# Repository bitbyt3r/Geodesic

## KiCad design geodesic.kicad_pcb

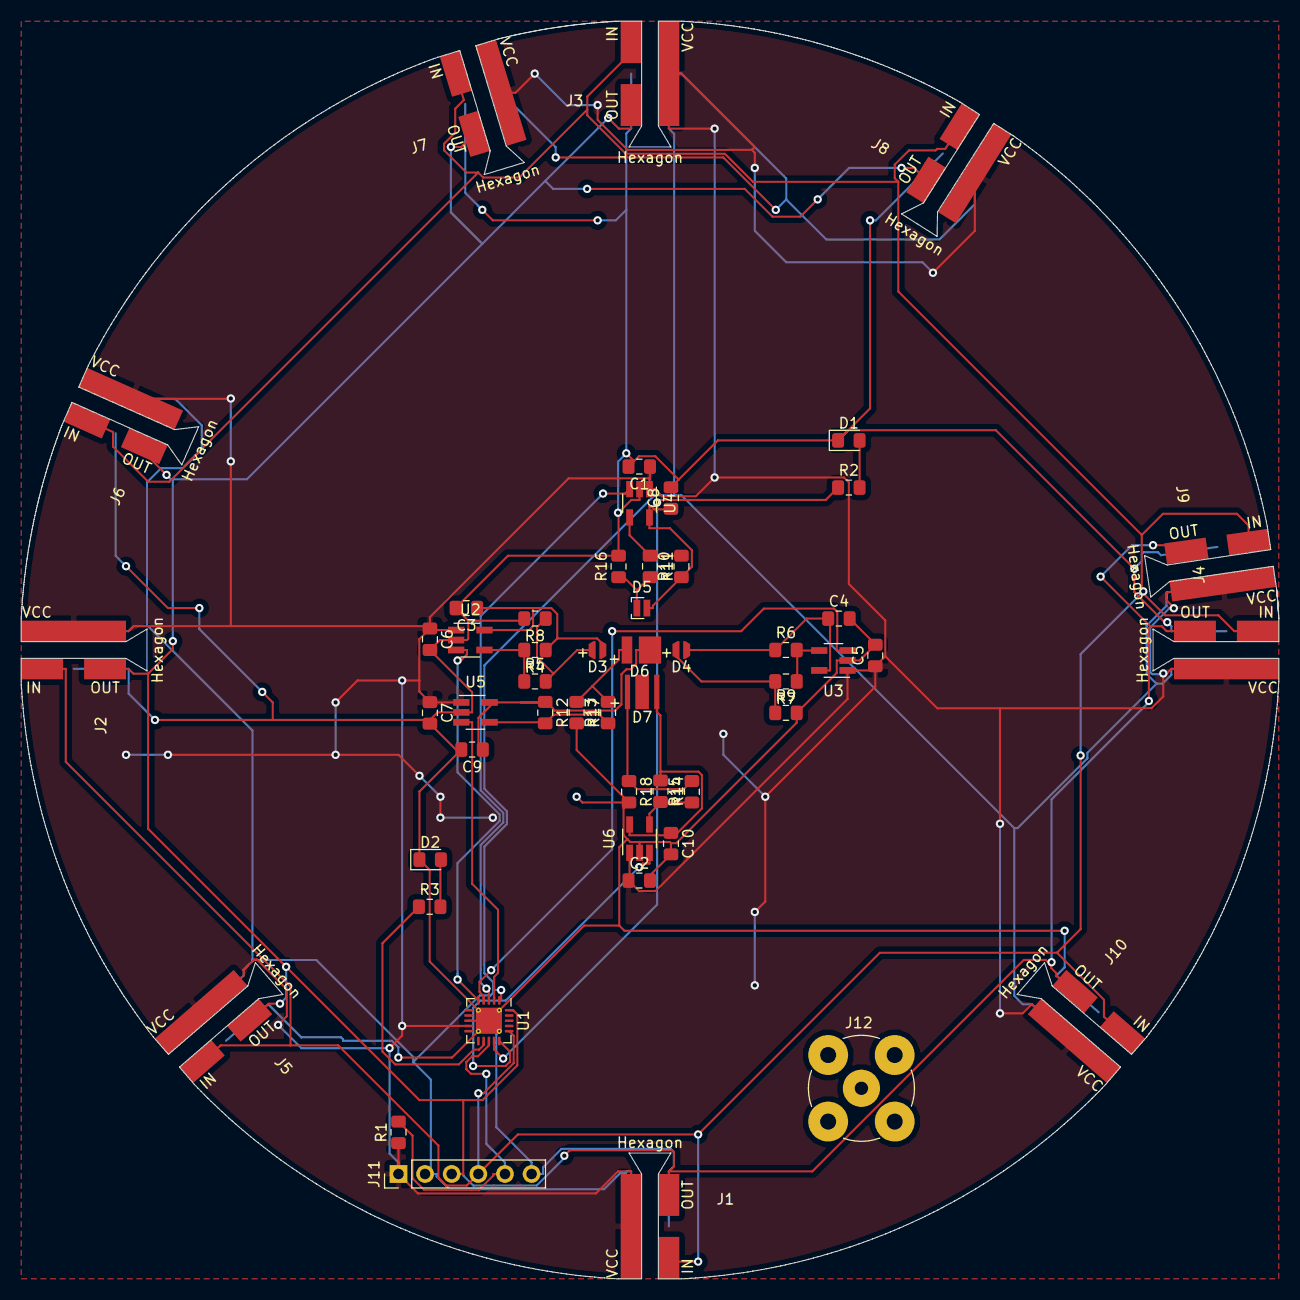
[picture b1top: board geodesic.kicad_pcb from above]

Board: 2 copper layers, 120.0 x 120.0 mm, 53 parts (0 on the bottom side), 30 nets.

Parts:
C1, C2, C5, C6, C7: 1uF; C_0805_2012Metric_Pad1.15x1.40mm_HandSolder
C3, C4, C8, C9, C10: 2.2uF; C_0805_2012Metric_Pad1.15x1.40mm_HandSolder
D1, D2: LED; LED_0805_2012Metric_Pad1.15x1.40mm_HandSolder
D3, D4: LED; XNOVA MP1616
D5: LED; LED_Cree-XQ
D6: LED; LUXEON_3535L
D7: LED; Cree_XPE
J1, J2, J3, J4, J5, J6, J7, J8, J9, J10: Hexagon; Geodesic_Hub_Connector
J11: Program; PinHeader_1x06_P2.54mm_Vertical
J12: AudioJack2_Ground; BNC_TEConnectivity_1478204_Vertical
R1: 1k; R_0805_2012Metric_Pad1.15x1.40mm_HandSolder
R2, R3, R4, R5, R6, R7, R8, R9, R10, R11, R12, R13, R14, R15, R16, R17, R18: R; R_0805_2012Metric_Pad1.15x1.40mm_HandSolder
U1: ATtiny24A-MU; QFN-20-1EP_4x4mm_P0.5mm_EP2.5x2.5mm_ThermalVias
U2, U3, U4, U5, U6: PAM2800; SOT-23-5_HandSoldering

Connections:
+5V: C1.1, C2.1, C5.1, C6.1, C7.1, J1.1, J2.1, J3.1, J4.1, J5.1, J6.1, J7.1, J8.1, J9.1, J10.1, J11.1, R1.1, U1.9, U2.1, U3.1, U4.1, U5.1, U6.1
/Clock: J1.2, J2.2, J3.2, J4.2, J5.2, J6.2, J7.2, J8.2, J9.2, J10.2, J11.2, U1.1
/Data_In: J1.3, J2.3, J3.3, J4.3, J5.3, J6.3, J7.3, J8.3, J9.3, J10.3, J11.4, U1.16
/Data_Out: J1.4, J2.4, J3.4, J4.4, J5.4, J6.4, J7.4, J8.4, J9.4, J10.4, J11.3, U1.20
/Reset: J11.5, R1.2, U1.13
GND: C1.2, C2.2, C3.2, C4.2, C5.2, C6.2, C7.2, C8.2, C9.2, C10.2, D1.1, D2.1, J1.5, J2.5, J3.5, J4.5, J5.5, J6.5, J7.5, J8.5, J9.5, J10.5, J11.6, R8.2, R9.2, R16.2, R17.2, R18.2, U1.8, U1.21, U2.2, U3.2, U4.2, U5.2, U6.2
unnamed: C3.1, D3.2, R4.1, U2.5
unnamed: C4.1, D4.2, R6.1, U3.5
unnamed: C8.1, D5.2, R10.1, U4.5
unnamed: C9.1, D6.2, R12.1, U5.5
unnamed: C10.1, D7.2, R14.1, U6.5
unnamed: D1.2, R2.2
unnamed: D2.2, R3.2
unnamed: D3.1, R5.2, R8.1
unnamed: D4.1, R7.2, R9.1
unnamed: D5.1, R11.2, R16.1
unnamed: D6.1, R13.2, R17.1
unnamed: D7.1, R15.2, R18.1
unnamed: R2.1, U1.14
unnamed: R3.1, U1.12
unnamed: R4.2, R5.1, U2.4
unnamed: R6.2, R7.1, U3.4
unnamed: R10.2, R11.1, U4.4
unnamed: R12.2, R13.1, U5.4
unnamed: R14.2, R15.1, U6.4
unnamed: U1.2, U5.3
unnamed: U1.3, U4.3
unnamed: U1.4, U3.3
unnamed: U1.5, U2.3
unnamed: U1.15, U6.3

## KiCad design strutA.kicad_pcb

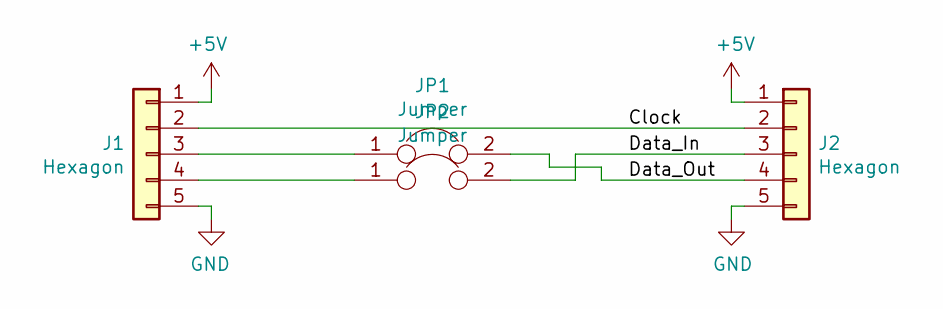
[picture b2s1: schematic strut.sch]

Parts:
J1, J2: Hexagon; Spoke_Connector
JP1, JP2: Jumper; SolderJumper-2_P1.3mm_Open_RoundedPad1.0x1.5mm

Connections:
+5V: J1.1, J2.1
/Clock: J1.2, J2.2
/Data_In: J2.3, JP2.2
/Data_Out: J2.4, JP1.2
GND: J1.5, J2.5
unnamed: J1.3, JP1.1
unnamed: J1.4, JP2.1

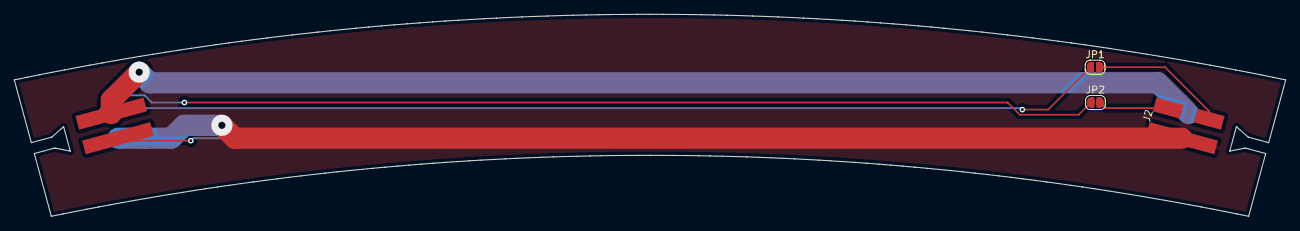
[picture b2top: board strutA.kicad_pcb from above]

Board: 2 copper layers, 180.0 x 28.6 mm, 4 parts (1 on the bottom side), 7 nets.

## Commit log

2018-11-21 Created hub
2018-11-21 Fixed out line and reduced diameter
2018-11-21 Added spoke connector
2018-11-21 Starting to construct the strut
2018-11-21 Exported step files
2018-11-22 Now with the proper angles
2018-11-22 Finished struts
2018-11-24 Added vrml
2018-11-24 Bumped steps
2018-11-24 Updated step
2018-11-24 Layed out pcb
2018-11-25 Added gerbers
